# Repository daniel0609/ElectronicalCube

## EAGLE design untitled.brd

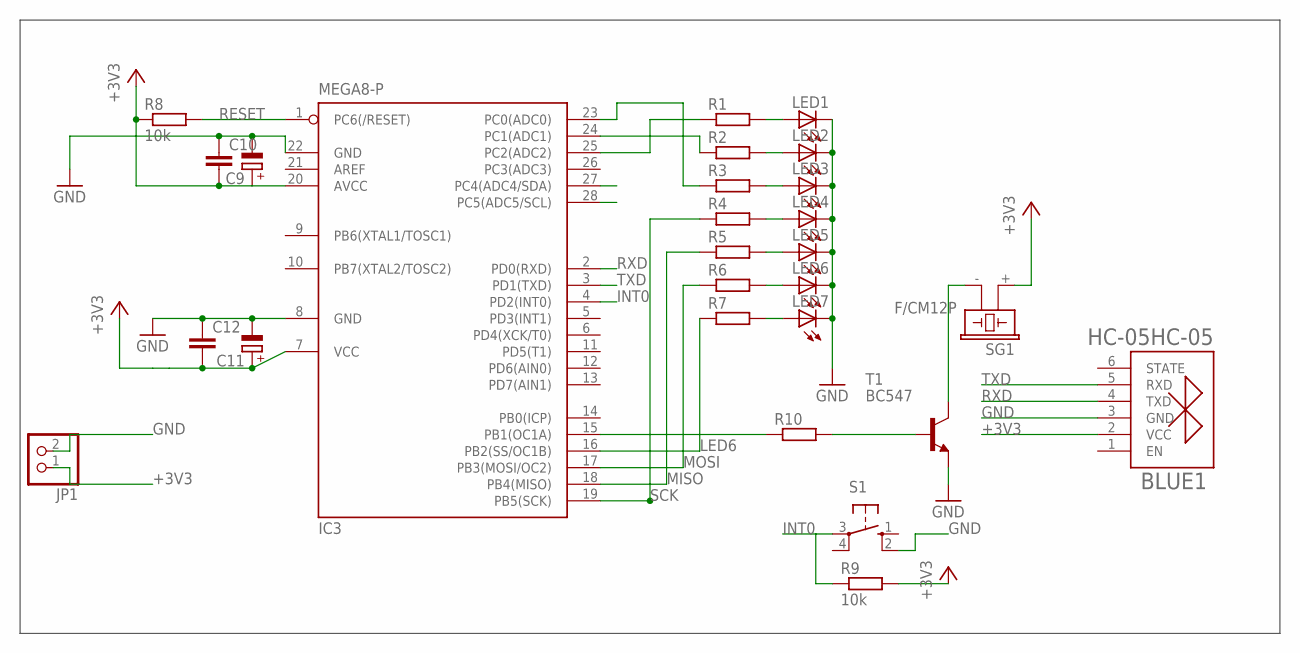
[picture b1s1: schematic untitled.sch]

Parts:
BLUE1: HC-05HC-05; HC-05
C9, C11: CPOL-EUE1.8-4; E1,8-4
C10, C12: C-EU025-024X044; C025-024X044
IC3: MEGA8-P; DIL28-3
JP1: PINHD-1X2; 1X02
LED1, LED2, LED3, LED4, LED5, LED6, LED7: LED5MM
R1, R2, R3, R4, R5, R6, R7, R10: R-EU_0204/7; 0204/7
R8: 10k; 0204/7
R9: 10k; 0207/10
S1: 10-XX; B3F-10XX
SG1: F/CM12P
T1: BC547; TO92

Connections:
+3V3: BLUE1.2 (VCC), C9.+, C10.2, C11.+, C12.2, IC3.7 (VCC), IC3.20 (AVCC), JP1.1, R8.1, R9.2, SG1.+ (1)
GND: BLUE1.3 (GND), C9.-, C10.1, C11.-, C12.1, IC3.8 (GND), IC3.22 (GND), JP1.2, LED1.K (C), LED2.K (C), LED3.K (C), LED4.K (C), LED5.K (C), LED6.K (C), LED7.K (C), S1.2 (S1), T1.1 (E)
INT0: IC3.4 (PD2(INT0)), R9.1, S1.3
LED6: IC3.16 (PB2(SS/OC1B)), R7.1
MISO: IC3.18 (PB4(MISO)), R5.1
MOSI: IC3.17 (PB3(MOSI/OC2)), R6.1
unnamed: LED4.A, R4.2
unnamed: LED5.A, R5.2
unnamed: LED6.A, R6.2
unnamed: LED7.A, R7.2
unnamed: LED1.A, R1.2
unnamed: IC3.25 (PC2(ADC2)), R1.1
unnamed: IC3.24 (PC1(ADC1)), R2.1
unnamed: IC3.15 (PB1(OC1A)), R10.1
unnamed: R10.2, T1.2 (B)
unnamed: SG1.- (2), T1.3 (C)
unnamed: IC3.23 (PC0(ADC0)), R3.1
unnamed: LED2.A, R2.2
unnamed: LED3.A, R3.2
RESET: IC3.1 (PC6(/RESET)), R8.2
RXD: BLUE1.4 (TXD), IC3.2 (PD0(RXD))
SCK: IC3.19 (PB5(SCK)), R4.1
TXD: BLUE1.5 (RXD), IC3.3 (PD1(TXD))

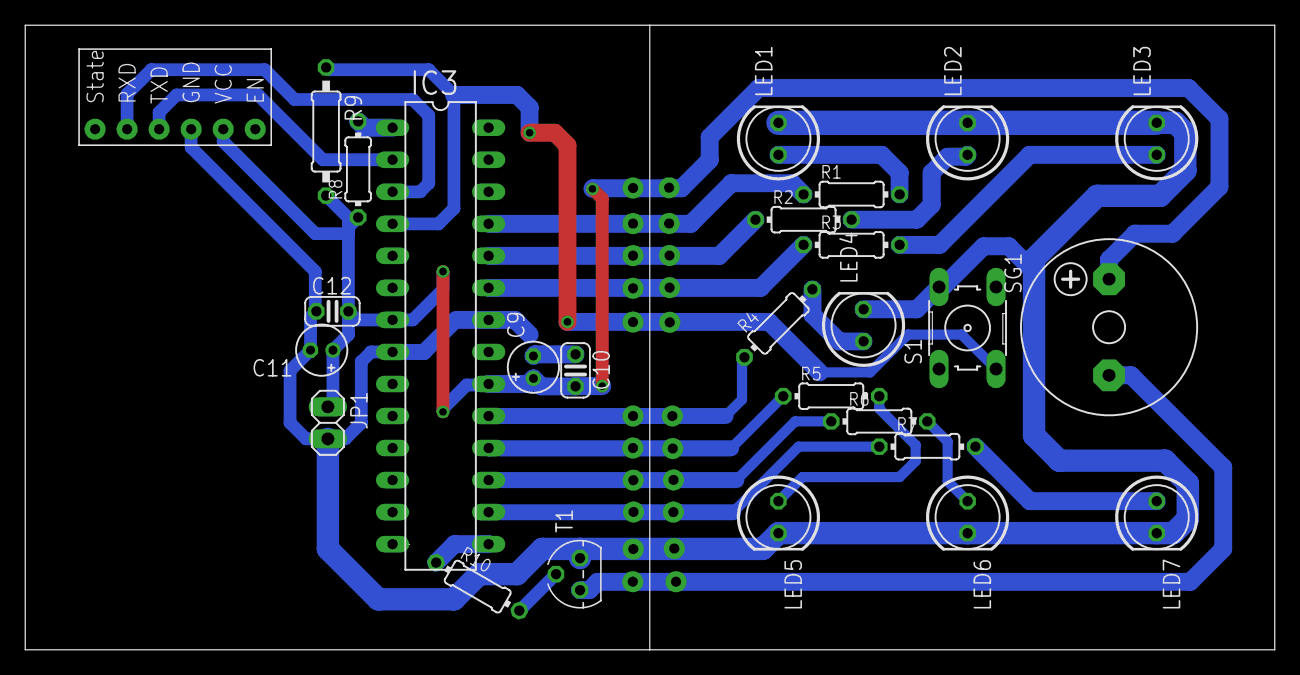
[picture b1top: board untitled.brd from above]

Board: 2 copper layers, 99.1 x 49.5 mm, 27 parts (0 on the bottom side), 23 nets.

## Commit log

2017-09-09 board done
